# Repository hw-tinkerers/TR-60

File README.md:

# TR-60
TR-60 is a 60% custom mechanical keyboard PCB that is inspired by the  [bakeneko](https://github.com/kkatano/bakeneko-60) PCB but adds a couple of improvements to it.

1. TR-60 adds BLE support to the PCB so that it can be used wirelessly.
2. Add tray mount compatible holes to be used with keyboard cases like [Salvation](https://ilumkb.com/products/wilba-tech-salvation-keyboard)

TR-60 stands for typewriter-60.

The repository contains the KICAD files of the keyboard PCB design with an nRF chip and this PCB is one of the first PCB to be built around the nRF52840 bare chip and not around any module.

<strong>Front View (Rendering)</strong>

<strong>Back View (Rendering)</strong>

<strong>Front View of PCB</strong>.

<strong>Back View of PCB</strong>.

<strong>Front View fully assembled with keycaps</strong>.

<strong>Back View fully assembled with battery</strong>.

<strong>Fully assembled with Bakeneko case</strong>.

The PCB is designed in such a way that is compatible with both nRF52840 and nRF52833 MCUs as they have the same pinouts and the NC pins on nRF53833 are being used in nRF52840 making it compatible with both MCUs to mitigate supply shortage problems.

The PCB has a board antenna for BLE and an onboard charger chip BQ24075 (also compatible with BQ24073 and BQ24074) with a JST (1mm) connector for lipo battery (But the 1mm JST connector is non-conventional and will be changed to a more mainstream connector with 2.54mm pitch with which most lipo batteries are shipped). A lipo battery of 200-1000mAh can be used with the PCB. (Note: Tested only with 300mAH battery, but up to 1000mAH should not be a problem. But do it at your own risk)

The PCB has a SWD 10-pin debug connector compatible with [tag-connect](https://www.tag-connect.com/product/tc2050-idc-nl-050-all) 10-pin debug connector for flashing firmware.
The board also supports an Adafruit-UF2 bootloader to upload firmware through the USB type-C connector (If a PCB is bought from us). You can find how to build and flash the UF2 bootloader to the board in an upcoming tutorial. (still under making)

You can also order your PCB from JLC PCB with the Gerber and BOM files provided in the repository in the production folder. The video guide on how to order from JLC will be up soon.

The board supports [ZMK](https://zmk.dev/) firmware for USB and BLE connectivity. The hardware definition for the nRF52 chip is written and the guide to customize the keymap to customize the keys for the keyboard can be found below. 

The firmware can be built directly on GitHub using GitHub actions and also a local toolchain can be set up on your computer to build firmware. Both the links can be found below.

1. [Local Toolchain setup](https://github.com/hw-tinkerers/zmk)
2. [Github Actions](https://github.com/hw-tinkerers/tr60-zmk-config)

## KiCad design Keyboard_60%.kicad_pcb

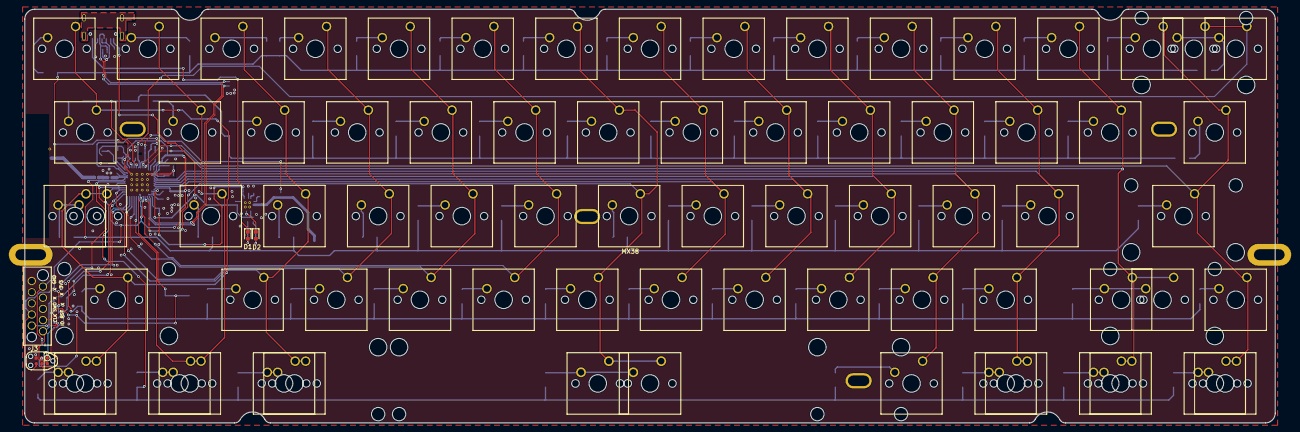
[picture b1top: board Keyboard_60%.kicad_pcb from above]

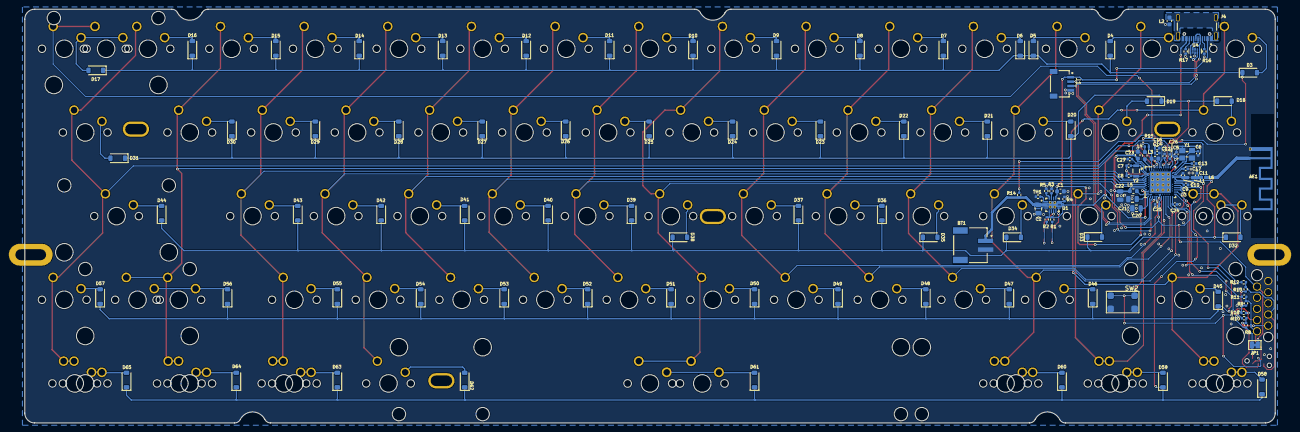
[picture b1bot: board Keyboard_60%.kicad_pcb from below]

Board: 2 copper layers, 284.7 x 94.2 mm, 200 parts (119 on the bottom side), 126 nets.

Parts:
AE1: Antenna_Shield; BLE_ANTENNA
BT1: Lipo cell; JST-2-pin
C1, C14, C23: 1uF; C_0603_1608Metric
C2, C20, C21, C22: 4u7F; C_0805_2012Metric
C5, C6, C7, C8: 8pF; C_0402_1005Metric
C9: 820pF; C_0402_1005Metric
C10: 1pF; C_0402_1005Metric
C11: 1.2pF; C_0402_1005Metric
C12: DNP; C_0402_1005Metric
C13: 100pF; C_0402_1005Metric
C16, C17, C24, C25, C26, C27: 100nF; C_0402_1005Metric
D1, D2: LED; LED_0603_1608Metric
D3, D4, D5, D6, D7, D8, D9, D10, D11, D12, D13, D14, D15, D16, D17, D18, D19, D20, D21, D22, D23, D24, D25, D26, D27, D28, D29, D30, D31, D32, D33, D34, D35, D36, D37, D38, D39, D40, D41, D42, D43, D44, D45, D46, D47, D48, D49, D50, D51, D52, D53, D54, D55, D56, D57, D58, D59, D60, D61, D62, D63, D64, D65: 1N4148W; D_SOD-123
J1: JST-4-pin
J3: Prog_conn; DB_CONN
J4: TYPE-C-31-M12_13; tyye_c_connector
J5: Tag connect TC2030-CTX; TC2030-IDC-NL
JP1: SolderJumper; SolderBridge
L1: 4.7nH; L_0402_1005Metric
L2: 60R@100MHz; L_0603_1608Metric
L3, L5: 10uH; L_0603_1608Metric
L4: 15nH; L_0402_1005Metric
L6: 2.2nH; L_0402_1005Metric
MX1, MX2, MX3, MX4, MX5, MX6, MX7, MX8, MX9, MX10, MX11, MX12, MX13, MX14, MX15, MX18, MX19, MX20, MX21, MX22, MX23, MX24, MX25, MX26, MX27, MX28, MX29, MX33, MX34, MX35, MX36, MX37, MX38, MX39, MX40, MX41, MX42, MX43, MX46, MX47, MX48, MX49, MX50, MX51, MX52, MX53, MX54, MX55, MX57, MX68, MX72: 1u; SW_Cherry_MX_1.00u_PCB
MX16: 2u; SW_Cherry_MX_2.00u_PCB
MX17, MX30, MX67, MX69, MX71, MX73: 1.5u; SW_Cherry_MX_1.50u_PCB
MX31, MX56: 1.75u; SW_Cherry_MX_1.75u_PCB
MX32, MX59, MX60, MX61, MX63, MX64, MX65, MX66: 1.25u; SW_Cherry_MX_1.25u_PCB
MX44, MX45: 2.25u; SW_Cherry_MX_2.25u_PCB
MX58: 2.75u; SW_Cherry_MX_2.75u_PCB
MX62: 6.25u; SW_Cherry_MX_6.25u_PCB
MX70: 7u; SW_Cherry_MX_7.00u_PCB
R1, R2, R4: 1k2; R_0402_1005Metric
R3: 8k2; R_0402_1005Metric
R5, R16, R17: 5k1; R_0402_1005Metric
R8, R9, R13, R14, R15, R18: 10k; R_0402_1005Metric
R10, R11, R12: 22E; R_0402_1005Metric
S1: Open Hardware; OSHW-Logo
S2: Keybaord_outline_edgecuts
S3: BLE-symbol
S4: ZMK_logo
SW2: Reset Switch; RST_SW
TH1: 10k; R_0402_1005Metric
U1: BQ24074RGTR; QFN-16
U3: nRF52840-QIAA-R/nRF52833-QIAA-R; aqfn73
U4: TPD4E05U06DQAR; USON-10
Y1: 32MHz; SMD-4_crystal
Y2: 32.768kHz; SMD-2_crystal

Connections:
/ANT_FEED: AE1.1 (A), L6.2
/COL0: MX1.2 (B), MX17.2 (B), MX31.2 (B), MX32.2 (B), MX45.2 (B), MX59.2 (B), MX67.2 (B), U3.U24 (P1.04)
/COL1: MX2.2 (B), MX18.2 (B), MX33.2 (B), MX60.2 (B), MX68.2 (B), U3.AD16 (P0.20)
/COL2: MX3.2 (B), MX19.2 (B), MX34.2 (B), MX46.2 (B), MX61.2 (B), MX69.2 (B), U3.W24 (P1.02)
/COL3: MX4.2 (B), MX20.2 (B), MX35.2 (B), MX47.2 (B), U3.AD20 (P0.24)
/COL4: MX5.2 (B), MX21.2 (B), MX36.2 (B), MX48.2 (B), U3.AD18 (P0.22)
/COL5: MX6.2 (B), MX22.2 (B), MX37.2 (B), MX49.2 (B), U3.AD10 (P0.15)
/COL6: MX7.2 (B), MX23.2 (B), MX38.2 (B), MX50.2 (B), MX62.2 (B), MX70.2 (B), U3.AD8 (P0.13)
/COL7: MX8.2 (B), MX24.2 (B), MX39.2 (B), MX51.2 (B), U3.R1 (P1.09/TRACEDATA3)
/COL8: MX9.2 (B), MX25.2 (B), MX40.2 (B), MX52.2 (B), U3.N1 (P0.08)
/COL9: MX10.2 (B), MX26.2 (B), MX41.2 (B), MX53.2 (B), U3.L1 (P0.06)
/COL10: MX11.2 (B), MX27.2 (B), MX42.2 (B), MX54.2 (B), MX63.2 (B), U3.J1 (P0.04/AIN2)
/COL11: MX12.2 (B), MX28.2 (B), MX43.2 (B), MX55.2 (B), MX64.2 (B), MX71.2 (B), U3.G1 (P0.26)
/COL12: MX13.2 (B), MX29.2 (B), MX56.2 (B), MX58.2 (B), MX65.2 (B), MX72.2 (B), U3.A8 (P0.31/AIN7)
/COL13: MX14.2 (B), MX30.2 (B), MX44.2 (B), MX57.2 (B), MX66.2 (B), MX73.2 (B), U3.A10 (P0.29/AIN5)
/COL14: MX15.2 (B), MX16.2 (B), U3.A14 (P1.15)
/DB_SWDCLK: J3.1, J5.4, R8.1, R10.1
/DB_SWDIO: J3.6, J5.2, R9.1, R11.1
/DB_SWO: J3.2, J5.6, R12.1, R13.1
/ROW0: D3.1 (K), D4.1 (K), D5.1 (K), D6.1 (K), D7.1 (K), D8.1 (K), D9.1 (K), D10.1 (K), D11.1 (K), D12.1 (K), D13.1 (K), D14.1 (K), D15.1 (K), D16.1 (K), D17.1 (K), U3.A20 (P1.10)
/ROW1: D18.1 (K), D19.1 (K), D20.1 (K), D21.1 (K), D22.1 (K), D23.1 (K), D24.1 (K), D25.1 (K), D26.1 (K), D27.1 (K), D28.1 (K), D29.1 (K), D30.1 (K), D31.1 (K), U3.A16 (P1.13)
/ROW2: D32.1 (K), D33.1 (K), D34.1 (K), D35.1 (K), D36.1 (K), D37.1 (K), D38.1 (K), D39.1 (K), D40.1 (K), D41.1 (K), D42.1 (K), D43.1 (K), D44.1 (K), U3.J24 (P0.10/NFC2)
/ROW3: D45.1 (K), D46.1 (K), D47.1 (K), D48.1 (K), D49.1 (K), D50.1 (K), D51.1 (K), D52.1 (K), D53.1 (K), D54.1 (K), D55.1 (K), D56.1 (K), D57.1 (K), U3.L24 (P0.09/NFC1)
/ROW4: D58.1 (K), D59.1 (K), D60.1 (K), D61.1 (K), D62.1 (K), D63.1 (K), D64.1 (K), D65.1 (K), U3.R24 (P1.06)
/USB and Power management/V_BATT: BT1.1 (+), C2.1, R14.2, U1.2 (BAT_2), U1.3 (BAT_3)
/USB_D+: J1.3, J4.A6 (D+), J4.B6 (D+), U3.AD6 (D+), U4.1 (IO1), U4.4 (D2+), U4.7 (NC), U4.10 (NC)
/USB_D-: J1.2, J4.A7 (D-), J4.B7 (D-), U3.AD4 (D-), U4.2 (IO2), U4.5 (D2-), U4.6 (NC), U4.9 (NC)
/VBATT_nRF: C16.1, R14.1, R15.2, U3.A12 (P0.02/AIN0)
/VBUS: C1.1, C20.1, J1.1, J4.A4 (VBUS), U1.13 (IN), U3.AD2 (VBUS)
/VDDH: J4.B4 (VBUS), R1.1, R2.1, U1.5 (EN2), U1.10 (OUT_10), U1.11 (OUT_11), U3.Y2 (VDDH)
/VDD_nRF: C22.1, C23.2, C24.1, C25.1, C26.1, J3.10, JP1.1 (A), L5.1, U3.A22 (VDD), U3.AD14 (VDD), U3.AD23 (VDD), U3.B1 (VDD), U3.W1 (VDD)
/~nReset: J3.7, J5.3, R18.1, SW2.1, U3.AC13 (P0.18/NRESET), U3.AD12 (P0.17)
GND: AE1.2 (Shield), BT1.2 (-), C1.2, C2.2, C5.1, C6.1, C7.1, C8.1, C9.1, C10.2, C11.2, C12.1, C13.1, C14.2, C16.2, C17.1, C20.2, C21.2, C22.2, C23.1, C24.2, C25.2, C26.2, C27.1, J1.4, J3.5, J4.A1 (GND), J4.B1 (GND), J5.5, L2.1, R3.1, R4.1, R5.2, R15.1, R16.2, R17.2, SW2.2, TH1.2, U1.4 (~CE), U1.6 (EN1), U1.8 (VSS), U1.17 (EXP), U3.74 (VSS), U3.74_1 (VSS), U3.74_2 (VSS), U3.74_3 (VSS), U3.74_4 (VSS), U3.74_5 (VSS), U3.74_6 (VSS), U3.74_7 (VSS), U3.74_8 (VSS), U3.74_9 (VSS), U3.74_10 (VSS), U3.74_11 (VSS), U3.74_12 (VSS), U3.74_13 (VSS), U3.74_14 (VSS), U3.74_15 (VSS), U3.74_16 (VSS), U3.B7 (VSS), U3.F23 (VSS_PA), U4.3 (GND), U4.8 (GND), Y1.2, Y1.4
GNDPWR: J4.S (SHIELD), L2.2
unnamed: C11.1, L1.2, L6.1
unnamed: D1.2 (A), R1.2
unnamed: D1.1 (K), U1.9 (~CHG)
unnamed: D2.2 (A), R2.2
unnamed: D2.1 (K), U1.7 (~PGOOD)
unnamed: D3.2 (A), MX1.1 (A)
unnamed: D4.2 (A), MX2.1 (A)
unnamed: D5.2 (A), MX3.1 (A)
unnamed: D6.2 (A), MX4.1 (A)
unnamed: D7.2 (A), MX5.1 (A)
unnamed: D8.2 (A), MX6.1 (A)
unnamed: D9.2 (A), MX7.1 (A)
unnamed: D10.2 (A), MX8.1 (A)
unnamed: D11.2 (A), MX9.1 (A)
unnamed: D12.2 (A), MX10.1 (A)
unnamed: D13.2 (A), MX11.1 (A)
unnamed: D14.2 (A), MX12.1 (A)
unnamed: D15.2 (A), MX13.1 (A)
unnamed: D16.2 (A), MX14.1 (A)
unnamed: D17.2 (A), MX15.1 (A), MX16.1 (A)
unnamed: D18.2 (A), MX17.1 (A)
unnamed: D19.2 (A), MX18.1 (A)
unnamed: D20.2 (A), MX19.1 (A)
unnamed: D21.2 (A), MX20.1 (A)
unnamed: D22.2 (A), MX21.1 (A)
unnamed: D23.2 (A), MX22.1 (A)
unnamed: D24.2 (A), MX23.1 (A)
unnamed: D25.2 (A), MX24.1 (A)
unnamed: D26.2 (A), MX25.1 (A)
unnamed: D27.2 (A), MX26.1 (A)
unnamed: D28.2 (A), MX27.1 (A)
unnamed: D29.2 (A), MX28.1 (A)
unnamed: D30.2 (A), MX29.1 (A)
unnamed: D31.2 (A), MX30.1 (A)
unnamed: D32.2 (A), MX31.1 (A), MX32.1 (A)
unnamed: D33.2 (A), MX33.1 (A)
unnamed: D34.2 (A), MX34.1 (A)
unnamed: D35.2 (A), MX35.1 (A)
unnamed: D36.2 (A), MX36.1 (A)
unnamed: D37.2 (A), MX37.1 (A)
unnamed: D38.2 (A), MX38.1 (A)
unnamed: D39.2 (A), MX39.1 (A)
unnamed: D40.2 (A), MX40.1 (A)
unnamed: D41.2 (A), MX41.1 (A)
unnamed: D42.2 (A), MX42.1 (A)
unnamed: D43.2 (A), MX43.1 (A)
unnamed: D44.2 (A), MX44.1 (A)
unnamed: D45.2 (A), MX45.1 (A)
unnamed: D46.2 (A), MX46.1 (A)
unnamed: D47.2 (A), MX47.1 (A)
unnamed: D48.2 (A), MX48.1 (A)
unnamed: D49.2 (A), MX49.1 (A)
unnamed: D50.2 (A), MX50.1 (A)
unnamed: D51.2 (A), MX51.1 (A)
unnamed: D52.2 (A), MX52.1 (A)
unnamed: D53.2 (A), MX53.1 (A)
unnamed: D54.2 (A), MX54.1 (A)
unnamed: D55.2 (A), MX55.1 (A)
unnamed: D56.2 (A), MX56.1 (A), MX58.1 (A)
unnamed: D57.2 (A), MX57.1 (A)
unnamed: D58.2 (A), MX59.1 (A), MX67.1 (A)
unnamed: D59.2 (A), MX60.1 (A), MX68.1 (A)
unnamed: D60.2 (A), MX61.1 (A), MX69.1 (A)
unnamed: D61.2 (A), MX62.1 (A), MX70.1 (A)
unnamed: D62.2 (A), MX63.1 (A)
unnamed: D63.2 (A), MX64.1 (A), MX71.1 (A)
unnamed: D64.2 (A), MX65.1 (A), MX72.1 (A)
unnamed: D65.2 (A), MX66.1 (A), MX73.1 (A)
unnamed: J4.A5 (CC1), R16.1
unnamed: J4.B5 (CC2), R17.1
unnamed: J5.1, JP1.2 (B), R8.2, R9.2, R13.2, R18.2
unnamed: L3.1, L4.2
unnamed: R4.2, U1.12 (ILIM)
unnamed: R3.2, U1.16 (ISET)
unnamed: R5.1, U1.15 (ITERM)
unnamed: TH1.1, U1.1 (TS)
unnamed: C10.1, L1.1, U3.H23 (ANT)
unnamed: L3.2, U3.B3 (DCC)
unnamed: L5.2, U3.AB2 (DCCH)
unnamed: C27.2, U3.C1 (DEC1)
unnamed: C12.2, U3.A18 (DEC2)
unnamed: C13.2, U3.D23 (DEC3)
unnamed: C14.1, C17.2, L4.1, U3.B5 (DEC4), U3.E24 (DEC6)
unnamed: C9.2, U3.N24 (DEC5)
unnamed: C21.1, U3.AC5 (DECUSB)
unnamed: C7.2, U3.D2 (P0.00/XL1), Y2.1
unnamed: C8.2, U3.F2 (P0.01/XL2), Y2.2
unnamed: R12.2, U3.AD22 (P1.00/SWO)
unnamed: R10.2, U3.AA24 (SWDCLK)
unnamed: R11.2, U3.AC24 (SWDIO)
unnamed: C6.2, U3.B24 (XC1), Y1.3
unnamed: C5.2, U3.A23 (XC2), Y1.1

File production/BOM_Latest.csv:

Designator,Footprint,Qty,Value,LCSC Part Number,MFR PN
BT1,keyboard:JST-2-pin,1,Lipo cell,C160402,SM02B-SRSS-TB(LF)(SN)
"C1, C14, C23",keyboard:C_0603_1608Metric,3,1uF,C1592,CL10A105KO8NNNC
"C2, C20, C21, C22",keyboard:C_0805_2012Metric,4,4u7F,C1779,CL21A475KAQNNNE
"C5, C6, C7, C8",keyboard:C_0402_1005Metric,4,8pF,C962144,AC0402CRNPO9BN8R0
C9,keyboard:C_0402_1005Metric,1,820pF,C107031,CC0402KRX7R9BB821
C10,keyboard:C_0402_1005Metric,1,1pF,C309455,CC0402BRNPO9BN1R0
C11,keyboard:C_0402_1005Metric,1,1.2pF,C327292,CC0402BRNPO9BN1R2
C13,keyboard:C_0402_1005Metric,1,100pF,C106200,CC0402JRNPO9BN101
"C16, C17, C24, C25, C26, C27",keyboard:C_0402_1005Metric,6,100nF,C1525,CL05B104KO5NNNC
"D3, D4, D5, D6, D7, D8, D9, D10, D11, D12, D13, D14, D15, D16, D17, D18, D19, D20, D21, D22, D23, D24, D25, D26, D27, D28, D29, D30, D31, D32, D33, D34, D35, D36, D37, D38, D39, D40, D41, D42, D43, D44, D45, D46, D47, D48, D49, D50, D51, D52, D53, D54, D55, D56, D57, D58, D59,  D60, D61, D62, D63, D64, D65",keyboard:D_SOD-123,63,1N4148W,C81598,1N4148W
J1,keyboard:JST-4-pin,1,JST-4-pin,C160404,SM04B-SRSS-TB(LF)(SN)
J4,keyboard:tyye_c_connector,1,TYPE-C-31-M12_13,C165948,TYPE-C-31-M-12
L1,keyboard:L_0402_1005Metric,1,4.7nH,C136252,MLK1005S4N7ST000
L2,keyboard:L_0603_1608Metric,1,60R@100MHz,C307775,MPZ1608S600ATDH5
"L3, L5",keyboard:L_0603_1608Metric,2,10uH,C3911082,LQM18DZ100M70L
L4,keyboard:L_0402_1005Metric,1,15nH,C86059,LQG15HS15NJ02D
L6,keyboard:L_0402_1005Metric,1,2.2nH,C5201668,BSCH001005052N2SCS
"R1, R2, R3, R4",keyboard:R_0402_1005Metric,4,1k2,C138040,RC0402FR-071K2L
"R5, R16, R17",keyboard:R_0402_1005Metric,3,5k1,C105872,RC0402FR-075K1L 
"R8, R9, R13, R14,R15, R18",keyboard:R_0402_1005Metric,6,10k,C60490,RC0402FR-0710KL
"R19, R20, R21, R22, R23",keyboard:R_0402_1005Metric,5,0E,C346504,HCJ0402ZT0R00
"R10, R11, R12",keyboard:R_0402_1005Metric,3,22E,C114765,RC0402FR-0722RL
SW1,keyboard:SPDT,1,MK-12C02-G025 ,C778186,MK-12C02-G025 
SW2,keyboard:RST_SW,1,Reset Switch,C388640,TS-1127-C
TH1,keyboard:R_0402_1005Metric,1,10k,C95939,SDNT1005X103F3950FTF
U1,keyboard:QFN-16,1,BQ24073RGTR,C15220,BQ24073RGTR
U3,keyboard:aqfn73,1,nRF52840-QIAA-R,C190794,nRF52840-QIAA-R
U4,keyboard:USON-10,1,TPD4E05U06DQAR,C138714,TPD4E05U06DQAR
Y1,keyboard:SMD-4_crystal,1,32MHz,C2149125,3TJ432000HYFBC
Y2,keyboard:SMD-2_crystal,1,32.768kHz,C97605,SC-32S32.768kHz20PPM9pF

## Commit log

2023-08-22 Added kicad files for V1.0 of TR-60
2023-08-23 Keyboard Case files
    Work in progress for Keyboard case files
2023-11-13 Changed Assets images
2023-11-13 Changes images for display
2023-11-13 Changed folder structure for Imgaes
2023-11-15 Gerber changed
2024-01-31 Added pictures of assembled keyboard and corrected typos in README file
2024-02-07 Added keyboard case file
2024-02-17 Finalized hardware Ver 1 release
2024-04-15 Added instructions to pair unpair device
2024-05-15 Exported edge cuts as footprint and set grid origin
2024-05-15 Completed routing for rows
2024-05-15 Completed routing for columns and rows for NRF
2024-05-15 Added charger circuit
2024-05-18 Solved all DRC and updated Versioning
